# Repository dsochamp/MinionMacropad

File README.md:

# Minion Micropad
My first macropad build! it contains a Raspberry Pi Pico, 9 MX Cherry switches, 2 rotary encoders and and OLED 128x64 screen alongside a custom silkscreen.

## The PCB

I routed my PCB using KiCad, and have uploaded my project alongside my schematic, PCB file as well as all my manafacturing files. This was my first time creating a custom PCB so it took a while to complete. Here is an image of the final design:

## CAD

I used Shapr3D to design the case for my Macropad, where I used its visualisation tool to see how it would look with certain materials and see how the glass panel would look in my design. I also made custom knobs for the rotary encoder and a stand for my OLED screen. Here is an image of how it looks unassembled with all the individual parts.

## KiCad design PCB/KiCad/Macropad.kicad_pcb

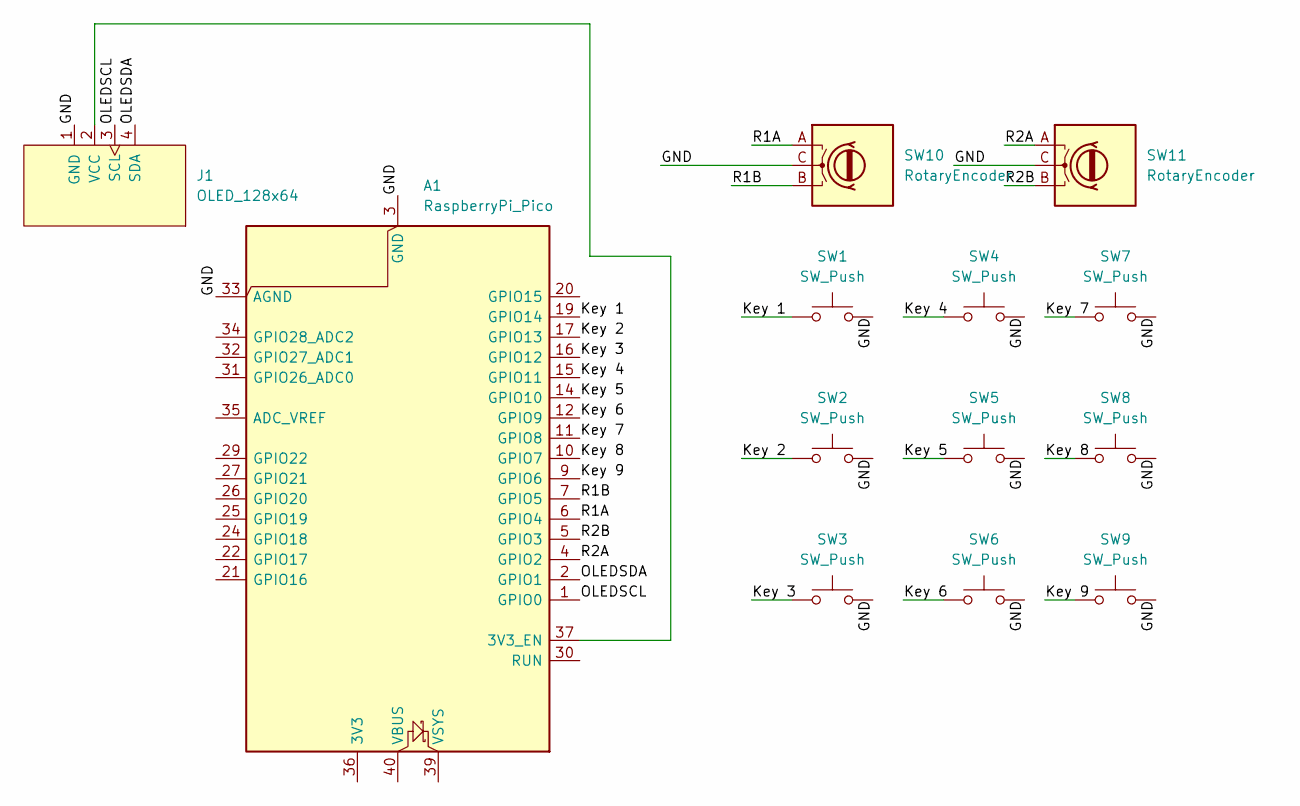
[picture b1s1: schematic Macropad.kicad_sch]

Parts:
A1: RaspberryPi_Pico; RaspberryPi_Pico_Common_Unspecified
J1: OLED_128x64
SW1, SW2, SW3, SW4, SW5, SW6, SW7, SW8, SW9: SW_Push; SW_Cherry_MX_1.00u_PCB
SW10, SW11: RotaryEncoder; RotaryEncoder_Alps_EC11E-Switch_Vertical_H20mm

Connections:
/GND: A1.3 (GND), A1.8 (GND), A1.13 (GND), A1.18 (GND), A1.23 (GND), A1.28 (GND), A1.33 (AGND), A1.38 (GND), J1.1 (GND), SW1.2, SW2.2, SW3.2, SW4.2, SW5.2, SW6.2, SW7.2, SW8.2, SW9.2, SW10.C, SW11.C
/Key 1: A1.19 (GPIO14), SW1.1
/Key 2: A1.17 (GPIO13), SW2.1
/Key 3: A1.16 (GPIO12), SW3.1
/Key 4: A1.15 (GPIO11), SW4.1
/Key 5: A1.14 (GPIO10), SW5.1
/Key 6: A1.12 (GPIO9), SW6.1
/Key 7: A1.11 (GPIO8), SW7.1
/Key 8: A1.10 (GPIO7), SW8.1
/Key 9: A1.9 (GPIO6), SW9.1
/OLEDSCL: A1.1 (GPIO0), J1.3 (SCL)
/OLEDSDA: A1.2 (GPIO1), J1.4 (SDA)
/R1A: A1.6 (GPIO4), SW10.A
/R1B: A1.7 (GPIO5), SW10.B
/R2A: A1.4 (GPIO2), SW11.A
/R2B: A1.5 (GPIO3), SW11.B
unnamed: A1.37 (3V3_EN), J1.2 (VCC)

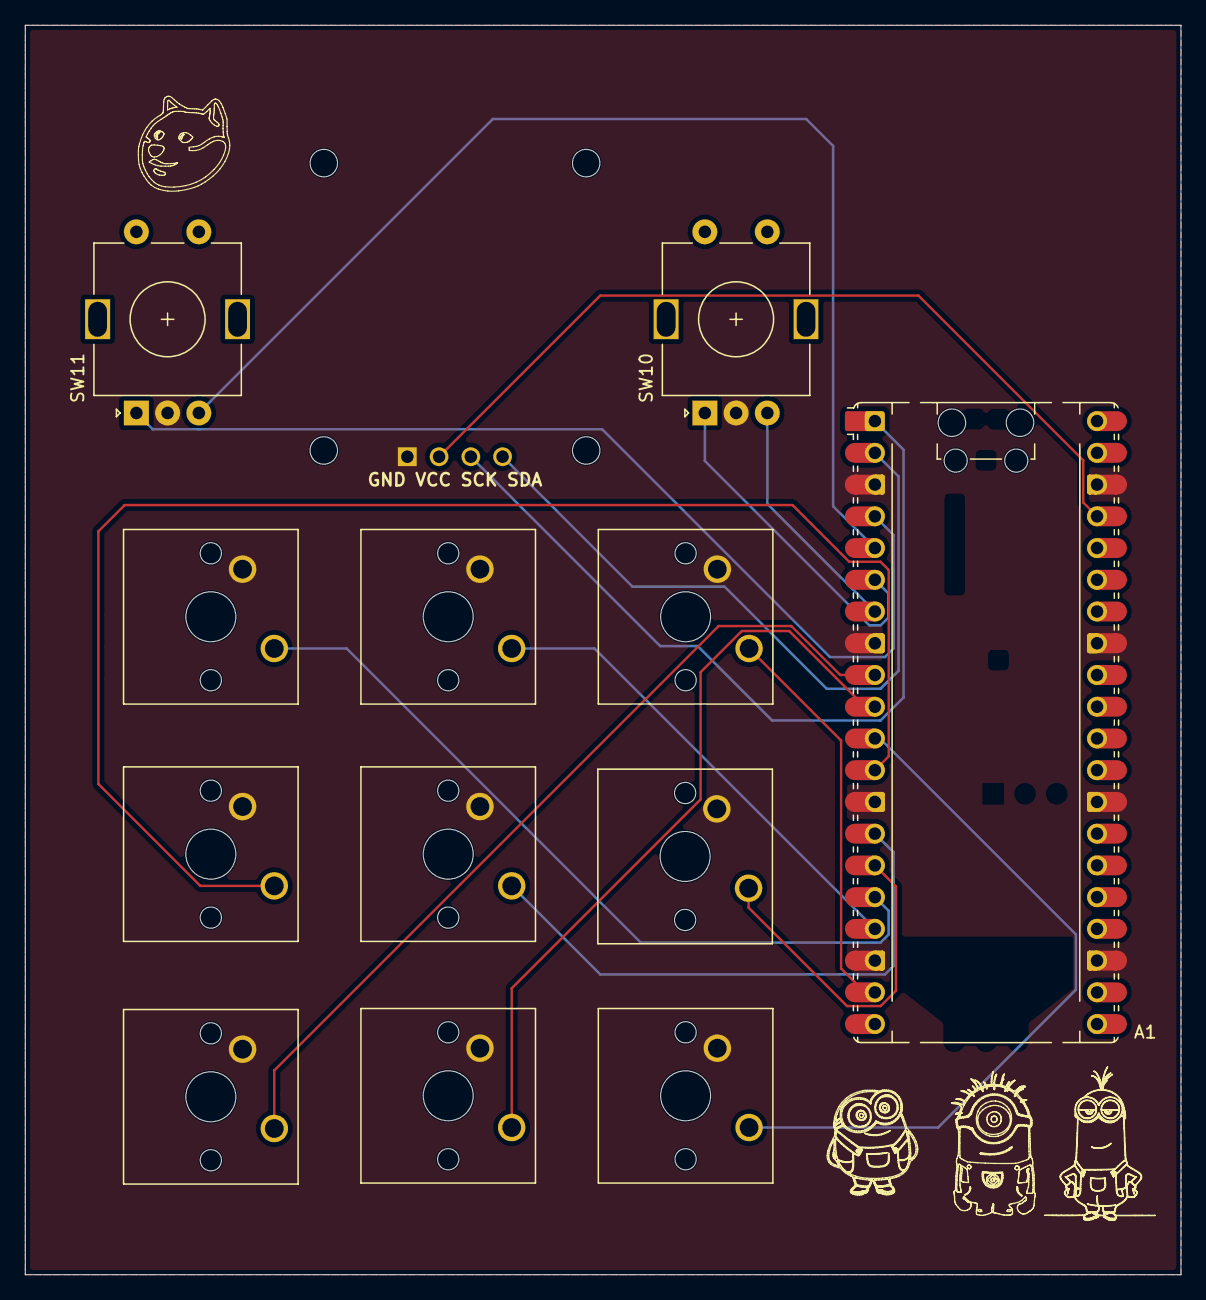
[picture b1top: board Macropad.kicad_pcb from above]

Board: 2 copper layers, 92.5 x 100.0 mm, 13 parts (1 on the bottom side), 17 nets.

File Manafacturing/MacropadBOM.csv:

"Id";"Designator";"Footprint";"Quantity";"Designation";"Supplier and ref";
1;"A1";"RaspberryPi_Pico_Common_Unspecified";1;"RaspberryPi_Pico";;;
2;"J1";"OLED_128x64";1;"OLED_128x64";;;
3;"SW1, SW2, SW3, SW4, SW5, SW6, SW7, SW8, SW9";"SW_Cherry_MX_1.00u_PCB";9;"SW_Push";;;
4;"SW10, SW11";"RotaryEncoder_Alps_EC11E-Switch_Vertical_H20mm";2;"RotaryEncoder";;;
